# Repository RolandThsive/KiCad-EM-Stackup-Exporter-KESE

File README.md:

<div align="center">

<picture>
  <source media="(prefers-color-scheme: dark)" srcset="docs/logo/Kese_Rectangular_DarkMode.svg">
  
</picture>

**Real 3D models of KiCad boards, with the true stack-up and the copper split per net.**
Give it a `.kicad_pcb` file, get every dielectric, every net's copper and every via at its true height, ready for an EM solver or a web viewer.

KiCad's 3D export is made for mechanical fit. An EM solver needs every core and prepreg as its own body with its εr
and tanδ, copper at its real thickness, and one closed solid per net for ports. KESE reads the `.kicad_pcb` directly
(no KiCad install needed) and writes exactly that for openEMS, or for Elmer and CalculiX through FreeCAD, with each copper solid named
after its net (`Copper_GND`) and the material values in `materials.json`. The same board also comes out as a light
surface model for web viewers and renders.

<sub>The RF sensor module of <code>Generator/Input/</code>, exported in visual mode.</sub>

</div>

> [!WARNING]
> **Fill your zones before exporting.** KESE uses the zone fills KiCad stores in the board file. A ground plane or
> copper pour that has not been filled (press **B** in KiCad) and saved is left out; `report.txt` counts it under
> "zones with no fill".

## Documentation

| I want to | Read |
|---|---|
| Start | [Getting Started](https://github.com/RolandThsive/KiCad-EM-Stackup-Exporter-KESE/wiki/Getting-Started), [Project Capabilities](https://github.com/RolandThsive/KiCad-EM-Stackup-Exporter-KESE/wiki/Project-Capabilities), [Examples](https://github.com/RolandThsive/KiCad-EM-Stackup-Exporter-KESE/wiki/Examples), [Time Distribution](https://github.com/RolandThsive/KiCad-EM-Stackup-Exporter-KESE/wiki/Time-Distribution) |
| Understand it | [Working Principle](https://github.com/RolandThsive/KiCad-EM-Stackup-Exporter-KESE/wiki/Working-Principle), [Stack-Up Model](https://github.com/RolandThsive/KiCad-EM-Stackup-Exporter-KESE/wiki/Stack-Up-Model), [Output Modes](https://github.com/RolandThsive/KiCad-EM-Stackup-Exporter-KESE/wiki/Output-Modes) |
| Export for my tool | [Choosing An Export](https://github.com/RolandThsive/KiCad-EM-Stackup-Exporter-KESE/wiki/Choosing-An-Export), [KiCad And Solver Compatibility](https://github.com/RolandThsive/KiCad-EM-Stackup-Exporter-KESE/wiki/Compatibility), [openEMS Workflow](https://github.com/RolandThsive/KiCad-EM-Stackup-Exporter-KESE/wiki/OpenEMS-Workflow) |
| Know what gets modelled | [Board](https://github.com/RolandThsive/KiCad-EM-Stackup-Exporter-KESE/wiki/Board), [Copper And Traces](https://github.com/RolandThsive/KiCad-EM-Stackup-Exporter-KESE/wiki/Copper-And-Traces), [Solder Masks](https://github.com/RolandThsive/KiCad-EM-Stackup-Exporter-KESE/wiki/Solder-Masks), [Silkscreens](https://github.com/RolandThsive/KiCad-EM-Stackup-Exporter-KESE/wiki/Silkscreens), [Finish](https://github.com/RolandThsive/KiCad-EM-Stackup-Exporter-KESE/wiki/Finish), [Colorizing](https://github.com/RolandThsive/KiCad-EM-Stackup-Exporter-KESE/wiki/Colorizing) |
| Look something up | [Parameter Reference](https://github.com/RolandThsive/KiCad-EM-Stackup-Exporter-KESE/wiki/Parameter-Reference), [Checks, Errors And Warnings](https://github.com/RolandThsive/KiCad-EM-Stackup-Exporter-KESE/wiki/Checks-Errors-And-Warnings), [Material Properties](https://github.com/RolandThsive/KiCad-EM-Stackup-Exporter-KESE/wiki/Material-Properties), [Project Output Organization](https://github.com/RolandThsive/KiCad-EM-Stackup-Exporter-KESE/wiki/Project-Output-Organization), [Feature Test Collection](https://github.com/RolandThsive/KiCad-EM-Stackup-Exporter-KESE/wiki/Feature-Test-Collection), [Glossary](https://github.com/RolandThsive/KiCad-EM-Stackup-Exporter-KESE/wiki/Glossary) |
| See what is next | [Future Upgrades And Planning](https://github.com/RolandThsive/KiCad-EM-Stackup-Exporter-KESE/wiki/Future-Upgrades-And-Planning) |

## Quick Start

```bash
cd Generator
python -m pip install -r requirements.txt

python run_KESE.py                                          # Every board in Input/: the defaults, set for RF work (below)
python run_KESE.py Input/rf_module.kicad_pcb                # One board: STEP in mm at KiCad's origin, with materials.json
python run_KESE.py board.kicad_pcb --for openems            # One STL per part in mm, with materials.json
python run_KESE.py board.kicad_pcb --for viewer             # The visible surface only, GLB for web viewers
python run_KESE.py board.kicad_pcb --set Finish.FINISH_TYPE=ENIG   # A finish for a board whose file names none
python run_KESE.py board.kicad_pcb --set Copper.VIA_WALL_MM=0.02
```

The defaults are the ones for an RF analysis, so a run with no option gives a model ready for a solver: simulation
mode, a STEP file in mm at KiCad's origin, one solid per net, every ply of the laminate a solid of its own, the solder
mask and the silkscreen left out, the finish the board file names, the Djordjevic-Sarkar model for the laminate and
the Huray model for the copper in `materials.json`, and the Verifier's checks at the end. A board whose file names no
finish stops with a message that says how to name one or leave it out.

Run every command from `Generator/`, which holds the program, its settings, `Input/` and `Output/`. Edit only the
files in `Generator/parameters/` (`PCB_elements/Stackup.py` says which parts of the board are built, and each element
has a file of its own beside it), or override one value for a single run with `--set`. Each run writes a new folder,
`Output/<board>/<mode>_<FORMATS>/`, with the model files, `materials.json` (role, layer, net, z range, εr, tanδ and
conductivity of every part), `parameters.txt` and `report.txt`, and never overwrites an earlier one. The pinned
packages need Python 3.12 or later. `python -m pip install .` gives a `kese` command that works
from any folder. Full walk-through: [Getting Started](https://github.com/RolandThsive/KiCad-EM-Stackup-Exporter-KESE/wiki/Getting-Started).

## What Works

- **Input:** `.kicad_pcb` files from KiCad 4 to 10, 1 to 8 copper layers, stack-up read from Board Setup (thickness,
  εr and tanδ of every core and of every prepreg ply, copper and mask thickness, the mask's material, colours,
  finish). Footprints are read from the board file, so no libraries are needed.
- **Copper:** tracks, arcs, pads of every shape, zone fills, copper graphics (solid or hatched) and text; one solid per
  net (default), per layer, or all merged; through, blind, buried and micro vias with plated barrels; KiCad 10's
  backdrills and covered, plugged, capped and filled vias; castellated holes and edge plating; optional etch trapezoid.
- **Board:** every dielectric a solid with its own εr and tanδ, resin filling the space beside inner copper, any
  outline from `Edge.Cuts` with cut-outs and boards inside them, plated and non-plated round and slotted holes,
  KiCad 10's counterbores and countersinks.
- **Plies:** the laminate is built as it is pressed (`Stackup.FUSION_BUILD = "PLIES_SEPARATE"`, the default): one
  solid for every prepreg ply, one for every core and one for the resin between the traces of each inner copper
  layer, each with its own thickness, εr and tanδ. `"PLIES_FUSED"` keeps one solid per gap between two copper
  layers and lists its plies in `materials.json`.
- **What is built:** `parameters/PCB_elements/Stackup.py` lists the board from the top silkscreen down to the bottom
  silkscreen, and each line is `True` (built) or `False` (left out), the top and the bottom side apart.
- **For the solver:** `materials.json` also gives the frequency each εr and tanδ holds at, a Djordjevic-Sarkar (the
  default) or tabulated model of how they change with frequency, the copper's roughness (Huray values by default, or
  Hammerstad), and for
  every copper part the foil, plating, etch factor and treated face of each layer it lies on.
- **Mask, silk and finish:** solder mask conformal over every trace, pulled back from the edge and open over every
  bore that no via protection shuts; silkscreen in KiCad's own stroke font and text layout, clipped off the pads;
  ENIG, ENEPIG, HASL, lead-free HASL, OSP, immersion silver and tin, and hard gold, each metal its own layer (on by
  default, and the type the board file names; the `top_finish`, `bottom_finish` and `hole_finish` lines of
  `Stackup.py`).
- **Two modes:** `simulation` writes closed solids that touch exactly and never overlap, as GLB, STEP, STL and OBJ;
  `visual` writes only the surface you can see, as GLB and OBJ, so nothing z-fights in a viewer.
- **STEP without a CAD kernel, meshes without a mesh library:** KESE builds its own meshes and writes STEP AP214,
  GLB, STL and OBJ itself, every part under its own name; it needs only `numpy`, `shapely` and `mapbox_earcut`.
  Holes, vias, round pads and arcs go into STEP as true circles and cylinders (`Step.STEP_EXACT_ARCS`, on by
  default), in files 2.5 to 3 times smaller than flat facets.
- **Presets:** `--for freecad`, `elmer`, `calculix`, `openems`, `viewer`, `blender_glb` or `blender_obj` set mode, formats, units, origin and grouping in one go (`parameters/Run_KESE/Presets.py`).
- **Checks:** the Verifier at the end of every run (closed solids, the same volume found four ways, no overlaps, one
  visible surface; `--no-verify` leaves it out) and a regression suite that runs 47 boards through every output before a pull request.
- **Not modelled yet:** component 3D models, text boxes, dimensions, images, rigid-flex.

Every feature and every parameter is in the wiki:
[Project Capabilities](https://github.com/RolandThsive/KiCad-EM-Stackup-Exporter-KESE/wiki/Project-Capabilities),
[Copper And Traces](https://github.com/RolandThsive/KiCad-EM-Stackup-Exporter-KESE/wiki/Copper-And-Traces),
[Parameter Reference](https://github.com/RolandThsive/KiCad-EM-Stackup-Exporter-KESE/wiki/Parameter-Reference) and
[Checks, Errors And Warnings](https://github.com/RolandThsive/KiCad-EM-Stackup-Exporter-KESE/wiki/Checks-Errors-And-Warnings).

<p align="center"><sub>24 of the feature test boards of <code>featureTest/</code>, each labelled with the KiCad features it
tests and exported in visual mode. Boards whose stack-up sets no colours are given a green mask and white silkscreen
for this picture. Left out are the boards of items KESE skips (19 and 19b), the same board in five KiCad formats (20a to 20e), the boards added after the picture was made (18c and 24 to 29d), and the example boards of the
<a href="https://github.com/RolandThsive/KiCad-EM-Stackup-Exporter-KESE/wiki/Examples">Examples</a> page.</sub></p>

## Status And Next Steps

- **Validation.** The models will be compared with measured boards and with reference solver results, and corrected
  wherever they disagree.
- **Solver imports.** The routes into openEMS, and into Elmer and CalculiX through FreeCAD, follow each tool's
  documented import formats and still have to be confirmed on each tool.
- **Planned:** a web application, a desktop application, maybe a KiCad add-on, and tighter integration with openEMS or
  other solvers.

## Contributing

Help with code, bug reports, test boards, solver checks, measurements and documentation is welcome. Read
[CONTRIBUTING.md](CONTRIBUTING.md) for the code layout, the rules every change keeps and the tests to run before a pull
request.

## Licensing

Hi Sassy boy Seth, There is no greedy man here.

KESE is **free software** under the [GNU General Public License, version 3 or later](LICENSE)
(`GPL-3.0-or-later`). You may run it for any purpose, commercial work included, and study, change and share it, as long
as what you share stays under the GPL with its source. The 3D models KESE writes from your own board are generally not
covered by the GPL, in the same way a document printed by a GPL program is not.

KESE includes material derived from KiCad, which is GPL-licensed: KiCad's "newstroke" stroke font and its text layout.
KiCad's original copyright headers are kept word for word in [`licenses/`](licenses) and listed in
[NOTICE.md](NOTICE.md). Contributions are accepted under the same license; see [CONTRIBUTING.md](CONTRIBUTING.md).

KESE was checked on thousands of KiCad boards from open hardware projects; no board is part of KESE. [credits.txt](https://github.com/RolandThsive/KiCad-EM-Stackup-Exporter-KESE/blob/corpus-testing/credits.txt)
thanks their authors and names each project's license, as does the wiki's
[Credits](https://github.com/RolandThsive/KiCad-EM-Stackup-Exporter-KESE/wiki/Credits) page.

**Contact (only through these channels):**
[Email](mailto:rolandthsive@yahoo.com) ·
[GitHub](https://github.com/RolandThsive) ·
[MyAnimeList](https://myanimelist.net/profile/RolandThsive) ·
[Instagram](https://www.instagram.com/ro_h_bots)

---

<div align="center">

## About Me

A traveller and mechatronics engineer who loves building machines that move, from the mechanics to the electronics
and the firmware. Trained in mechanical design and robotics, with a research master's in mechatronics, I have built
robotic hands, a humanoid torso, industrial bin-picking cells and rocket electronics, designing PCBs in KiCad and
firmware for STM32 and Espressif chips.

I put my full time into building industrial-grade software and making well-researched but hard-to-find scientific
knowledge free for everyone. KESE exists so that a board designed in KiCad can go straight into an EM solver without
being rebuilt by hand in CAD. I will keep maintaining it until it becomes the go-to bridge from KiCad to EM
simulation, with models that match real, fabricated boards.

**[Website](https://ro-h-bots.blogspot.com/)** ·
**[Instagram](https://www.instagram.com/ro_h_bots)** ·
**[MyAnimeList](https://myanimelist.net/profile/RolandThsive)** ·
**[Email](mailto:rolandthsive@yahoo.com)**

*Contributions of every kind are welcome. Together we can make this the reference tool for turning KiCad boards into
EM-ready models.*

</div>

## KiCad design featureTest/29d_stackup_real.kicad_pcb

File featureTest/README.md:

# Feature Test Boards

One small board per group of KiCad features that KESE reads. Each board is made by
`Generator/tests/feature_boards/make.py`; change a board there and run it again rather than
editing these files by hand:

```bash
cd Generator
python tests/feature_boards/make.py
```

The regression suite (`Generator/tests/test_boards.py`) runs every board here through every
output; after changing a board, run `python tests/test_boards.py --accept` to record it again.

Boards in KiCad 7's format were read back, zone-filled and saved by KiCad 7 itself, so they are
exactly what KiCad writes, including the outlines of TrueType text. That needs KiCad 7's Python
module (`pcbnew`): without it, `make.py` writes the boards as built, with unfilled zones, over the
saved ones (on a machine without KiCad, 31 files change). Run it where KiCad 7 is installed, or
put the saved boards back with `git checkout featureTest`. Features that only KiCad 8, 9 or 10
have are on hand-written boards in that version's format, written from KiCad's own file writer
source; open those once in that KiCad to confirm they load. One board (`29c`) is in the format
after KiCad 10, which a development build (10.99) writes: KESE reads it with a warning that the
format is newer than the ones it is tested with.

| File | Format | What it covers |
|---|---|---|
| `01_holes_slotted.kicad_pcb` | KiCad 7 (saved by KiCad 7) | Plated and non-plated slots: horizontal, vertical, rotated pad, rotated and flipped footprint, rectangular pad, long slot, a slot as wide as it is long, an offset slot. |
| `02_holes_round.kicad_pcb` | KiCad 7 (saved by KiCad 7) | Round plated holes of several sizes and pad shapes, an offset drill, non-plated holes with and without a copper ring, and a plated hole in a footprint on the back. |
| `03_vias_through.kicad_pcb` | KiCad 7 (saved by KiCad 7) | Through vias from 0.3 to 2 mm, a chain of vias on one net, vias in pads, a via on the board edge, a free via; vias left open in the mask (viasonmask true). |
| `03b_vias_k10.kicad_pcb` | KiCad 10 (hand-written) | KiCad 10's via options on four layers: tented on both sides, on the front only, open, and left to the board's setting on one side; covered, plugged, capped and filled vias; a backdrill from the bottom and one from the top, a counterbore and a countersink; blind, buried and micro vias; vias that keep only their start and end rings or drop unused rings; and a plated pad with a backdrill and mounting holes with a counterbore and a countersink. |
| `04_vias_blind_buried.kicad_pcb` | KiCad 7 (saved by KiCad 7) | Six layers: a through via, blind vias from each side, a buried via, and through vias and a plated pad that drop their unused rings. |
| `05_vias_micro.kicad_pcb` | KiCad 7 (saved by KiCad 7) | Eight layers: microvias on each side, a stack of microvias over a buried via, and the same levels staggered. |
| `06_padstacks.kicad_pcb` | KiCad 10 (hand-written) | KiCad 10's padstacks on four layers: a plated pad and a via with one shape on the front, another on the inner layers and a third on the back; a pad and a via with their own shape on every copper layer; a normal pad and via beside them, and inner tracks to the inner rings. |
| `07_pad_shapes.kicad_pcb` | KiCad 7 (saved by KiCad 7) | Every pad shape: circle, rect, oval, rounded rect, trapezoid, chamfered, chamfered and rounded, custom pads on a circle and a rect anchor; rotated pads, a footprint at 45 degrees and one on the back; mask-only and paste-only aperture pads, an edge-connector pad and a pad with no net. |
| `08_copper_graphics.kicad_pcb` | KiCad 7 (saved by KiCad 7) | Lines, rectangles, circles (open and filled), an arc, polygons (filled, open, and one with an arc edge) and a Bezier curve drawn on F.Cu and B.Cu with no net, as KiCad 7 has them; the same shapes in a footprint at 30 degrees and in one on the back; a track that ends on a drawing. |
| `08b_copper_graphics_nets.kicad_pcb` | KiCad 10 (hand-written) | KiCad 10's copper drawings: shapes that belong to a net, copper left bare by the solder mask (a rectangle, a track and an arc track, with and without a mask margin), rectangles with rounded corners, hatched, reverse-hatched and cross-hatched fills, and a board outline drawn as one rectangle with rounded corners. |
| `09_copper_text.kicad_pcb` | KiCad 7 (saved by KiCad 7) | Text on copper: the stroke font plain, bold, italic, rotated, on two lines and justified; TrueType text (DejaVu Sans) on F.Cu and mirrored on B.Cu, bold and italic; knockout text; a text box; footprint text with a hidden value and a ${REFERENCE} variable. |
| `10_tracks_arcs.kicad_pcb` | KiCad 7 (saved by KiCad 7) | Tracks 0.1 to 2 mm wide, arc tracks of 90 and 180 degrees and an almost straight one, a segment-arc-segment chain, a zero-length track, two nets that cross (a short), overlapping tracks of one net, a 1 um track, a T and an acute junction, tracks and an arc on B.Cu. The crossing tracks end on pads of their own nets: without them KiCad gives both the same net. |
| `11_zones.kicad_pcb` | KiCad 7 (saved by KiCad 7) | Four layers of zones: thermal reliefs and a solid connection to the same pads, pads that override the zone's connection, a pad of another net inside a zone, hatched fills at 0 and 45 degrees, a zone split in two by a track with its island kept on In1 and removed on In2, a zone on two layers with a cut-out, zones of two priorities overlapping, a zone left unfilled, and a keepout area that a zone flows around. |
| `12_outline_shapes.kicad_pcb` | KiCad 7 (saved by KiCad 7) | An outline of lines, rounded corners (arcs), a Bezier edge and a notch; cut-outs drawn as a circle, a rectangle, a polygon, a slot of two lines and two arcs, a rectangle of four lines whose ends miss by 3 nm, and a circle and a rectangle on Edge.Cuts inside a footprint at 30 degrees; zones on both sides that KiCad fills up to the outline and around the cut-outs. |
| `13a_outline_none.kicad_pcb` | KiCad 7 (saved by KiCad 7) | No Edge.Cuts at all: two plated pads joined by a track, and a via. |
| `13b_outline_two.kicad_pcb` | KiCad 7 (saved by KiCad 7) | Two separate boards in one file, one of them with a square hole that has a third, small board inside it. |
| `14_stackup_full.kicad_pcb` | KiCad 7 (saved by KiCad 7) | A four-layer stack-up with everything KiCad 7 lets you set: coloured mask and silk, a mask material with its permittivity, copper of 35, 17.5, 17.5 and 70 um, a prepreg of two sublayers, a core and a prepreg of different materials, an ENIG finish and impedance-controlled dielectrics. |
| `15_stackup_none.kicad_pcb` | KiCad 7 (saved by KiCad 7) | Four copper layers, no stack-up in the file (as older KiCad boards have), and a board thickness of 1.2 mm in the general section. |
| `16_edge_plating_castellation.kicad_pcb` | KiCad 7 (saved by KiCad 7) | Castellated pads (pad property castellated) on the right edge, with their holes on the edge, a plated board edge (edge_plating yes, castellated_pads yes) with GND tracks running along the left edge, a GND zone, and an immersion silver finish. |
| `16b_edge_plating_border.kicad_pcb` | KiCad 7 (saved by KiCad 7) | A plated board edge (edge_plating yes) as RF boards have it: a GND border 1.2 mm wide on every copper layer along the rounded outline and 1.0 mm wide around a rounded cut-out, the solder mask open over it on both sides, a fence of GND vias in the border, GND planes on F.Cu, In1.Cu and B.Cu, a +3V3 plane on In2.Cu, plated mounting holes, and a few parts. Green mask, white silk, ENIG. |
| `17_mask_silk.kicad_pcb` | KiCad 7 (saved by KiCad 7) | Solder mask openings from the board's pad-to-mask clearance, a footprint's margin, a pad's own margin and a negative one; plated pads; openings drawn on F.Mask and B.Mask (a rectangle over a track, a circle, a polygon, text); a tented via; silkscreen lines, shapes and text on both sides, TrueType silk text, and a silk outline drawn across pads. Red mask, black silk, lead-free HASL. |
| `17b_silk_over_copper.kicad_pcb` | KiCad 7 (saved by KiCad 7) | Silkscreen over copper: text and a line printed across four tracks 0.25 to 2 mm wide on F.Cu, and a line across the same tracks on B.Cu, so the ink rides over the mask on the copper; a footprint whose silk outline runs across its pads, a silk circle across a through-hole pad, and silk text across an opening drawn on F.Mask (for SILKSCREEN_OVER_COPPER). White mask, black silk, ENIG. |
| `18_finishes.kicad_pcb` | KiCad 7 (saved by KiCad 7) | Gold edge fingers: edge-connector pads on both sides running to a bevelled card edge (edge_connector bevelled), with a hard gold finish. |
| `18b_finish_pads.kicad_pcb` | KiCad 7 (saved by KiCad 7) | Surface finish on every kind of bare copper: an eight-pin SOIC-style footprint, a 3 mm square pad, a two-pin through-hole header (finish on both faces), a track left bare by an opening drawn on F.Mask, a tented via, and a round pad on the bottom. Pad-to-mask clearance 0.05 mm. Green mask, white silk, ENIG. |
| `18c_finish_before_mask.kicad_pcb` | KiCad 7 (saved by KiCad 7) | Surface finish applied before the solder mask (run with Finish.FINISH_BEFORE_SOLDER_MASK = True): SMD pads with the board's clearance and one with a negative mask margin, a track under the mask with silkscreen printed across it, a tented via to a round pad on the bottom, a through-hole header, and a GND zone on B.Cu with a thermal pad in it, so the finish lies on all the copper and the mask and ink lie on the finish. Blue mask, white silk, ENEPIG. |
| `19_skipped_items.kicad_pcb` | KiCad 7 (saved by KiCad 7) | Dimensions (aligned on F.Cu, orthogonal, leader, center and radial on silk), targets on F.Cu and silk, a group of a copper rectangle, a track and silk text, a footprint with a 3D model, a picture on silk, and text boxes on F.Cu and on silk. |
| `19b_skipped_items_k10.kicad_pcb` | KiCad 10 (hand-written) | KiCad 10's table (on F.Cu), QR codes on silk and on F.Cu, points on F.Cu and on a user layer, and a reference image. |
| `20a_format_kicad6.kicad_pcb` | KiCad 6 (hand-written) | The same small board in KiCad 6, 7, 8, 9 and 10's format: a plated pad and a rounded SMD pad in a footprint, a pad on the back of a turned footprint, a track, a via and an arc track, a GND zone on the back, and silkscreen and copper text. |
| `20b_format_kicad7.kicad_pcb` | KiCad 7 (saved by KiCad 7) | The same small board in KiCad 6, 7, 8, 9 and 10's format: a plated pad and a rounded SMD pad in a footprint, a pad on the back of a turned footprint, a track, a via and an arc track, a GND zone on the back, and silkscreen and copper text. |
| `20c_format_kicad8.kicad_pcb` | KiCad 8 (hand-written) | The same small board in KiCad 6, 7, 8, 9 and 10's format: a plated pad and a rounded SMD pad in a footprint, a pad on the back of a turned footprint, a track, a via and an arc track, a GND zone on the back, and silkscreen and copper text. |
| `20d_format_kicad9.kicad_pcb` | KiCad 9 (hand-written) | The same small board in KiCad 6, 7, 8, 9 and 10's format: a plated pad and a rounded SMD pad in a footprint, a pad on the back of a turned footprint, a track, a via and an arc track, a GND zone on the back, and silkscreen and copper text. |
| `20e_format_kicad10.kicad_pcb` | KiCad 10 (hand-written) | The same small board in KiCad 6, 7, 8, 9 and 10's format: a plated pad and a rounded SMD pad in a footprint, a pad on the back of a turned footprint, a track, a via and an arc track, a GND zone on the back, and silkscreen and copper text. |
| `24_backdrills.kicad_pcb` | KiCad 10 (hand-written) | KiCad 10's backdrills on six layers: from the back down to each inner layer and from the front (tertiary drills), both on one via, through the whole board, as wide as the pad, narrower than the hole, starting and ending on the same layer, on a blind via and through a track that leaves the drilled-out layer; plated pads with a backdrill and a tertiary drill, a non-plated hole stepped by one, and drills KESE leaves out as KiCad does: on an SMD pad, with no size, and to a layer the board does not have. |
| `25_post_machining.kicad_pcb` | KiCad 10 (hand-written) | KiCad 10's counterbores and countersinks on four layers. Mounting holes counterbored from the front and from the back, deeper than the board and to a floor inside an inner copper layer; countersunk at 82, 90, 100 and 120 degrees, from the back, to a depth short of the cone's tip, and smaller than the hole (nothing to cut). A plated pad counterbored on the front and countersunk on the back, a pad whose counterbore is centred on the pad off its offset drill, vias counterbored and countersunk, and what KESE leaves out as KiCad does: a counterbore with no depth, a countersink with no angle, and one on an SMD pad. |
| `26_via_protection.kicad_pcb` | KiCad 10 (hand-written) | KiCad 10's via protection (IPC-4761) on four layers: Types I to VII on the front, then on both faces (tented, tented and covered, plugged, plugged and covered, filled, filled and covered, filled and capped); a via left to the board's setting (plugged on the back), covered but not tented, capped with no fill, filled and backdrilled, plugged and counterbored on the same face, a filled blind via, a filled and capped buried via (a cap needs an outer end) and a blind via covered at its inner end (no effect). |
| `27_hatched_fills.kicad_pcb` | KiCad 10 (hand-written) | KiCad 10's hatched fills on two layers. Hatched, reverse-hatched and cross-hatched rectangles, a rectangle with rounded corners, circles and polygons on copper (with a net), silkscreen and the solder mask, at pen widths from 0.1 to 0.5 mm; copper left bare by the mask under a hatch; the hatch cut back around board text, a line, an overlapping hatched shape, a text box and another footprint's reference, but not around a footprint's own reference or another footprint's other text; a turned footprint with hatched drawings; a hatch too fine for its size, held to about 100 lines; a hatch drawn with no pen (nothing), a hatched custom pad shape (solid) and a hatched board outline (the outline only). |
| `28_plated_edge_machining.kicad_pcb` | KiCad 10 (hand-written) | KiCad 10's post machining, backdrills and blind vias at a plated board edge (edge_plating yes) on four layers: a counterbore from the front and a countersink from the back that cross the edge while their holes stay inside, a via backdrilled from the back and a plated pad drilled from the front (a tertiary drill) wider than their rings, both crossing the edge, and blind vias from the front that reach into the plating; GND tracks along the left edge give the plating its net. Each cuts the plating only between its own heights. |
| `29_stackup_plies.kicad_pcb` | KiCad 7 (saved by KiCad 7) | Six layers whose gaps are laid up of plies, as KiCad's stack-up editor writes them (the sub-layers of a dielectric): a 1080 ply on a 2116 ply under F.Cu and the same mirrored over B.Cu, a core of one ply, three equal 7628 plies between In2.Cu and In3.Cu, and a core with a bond film of half a micrometre, thinner than KESE builds on its own. A through via, a blind via from each side, a buried via through the three equal plies and one through both cores, a plated and a non-plated hole, a track on every layer and GND planes on In2.Cu and In3.Cu. |
| `29b_stackup_plies_machined.kicad_pcb` | KiCad 10 (hand-written) | KiCad 10's machining in a laminate of plies (four layers, a 2116 and a 1080 ply on each side of one core). Counterbores from the front, their depth from the top of F.Cu: to a floor inside the first ply (0.1 mm), exactly between the two plies (0.159 mm), inside the second ply (0.2 mm), inside In1.Cu and the resin beside it (0.243 mm) and inside the core (0.5 mm); the same from the back into the outer ply and to the join of the plies; a countersink from each side; vias with a backdrill and a tertiary drill through both plies, a counterbored via, blind vias through the plies and a buried via through the core, and a counterbored plated pad. |
| `29c_stackup_frequency.kicad_pcb` | KiCad 10.99 (hand-written) | What the format after KiCad 10 adds to every ply of a dielectric (file format 20260511): the frequency its er and loss tangent hold at (spec_frequency, in Hz) and how they change with frequency (dielectric_model constant or djordjevic_sarkar). Four layers: a 2116 ply with the Djordjevic-Sarkar model at 1 GHz on a 1080 ply with constant values, a core with the model at 10 GHz, a 1080 ply with the model at 5 GHz on a 2116 ply with constant values at 2.5 GHz, and a solder mask of another material on each side. |
| `29d_stackup_real.kicad_pcb` | KiCad 7 (saved by KiCad 7) | A fabricator's four-layer build as it is pressed (JLCPCB's JLC04161H-2116C, 1.6 mm): under each outer copper a 2116 ply of 0.124 mm (er 4.16) and a 1080 ply of 0.0764 mm (er 3.91), a core of 1.065 mm, inner copper of 15.2 um and outer copper of 35 um. A microstrip between two launch pads over a GND plane on In1.Cu, GND copper beside it with a fence of vias, a +3V3 plane on In2.Cu fed through a via, a decoupling capacitor, a header, and tracks on the back. Green mask, white silk, ENIG. |

## Example Boards

The three example boards of `Generator/Input/` are here too, so that the regression suite runs
them with the boards above. Each is a whole board that uses many of these features at once.
`make.py` does not make them, and does not write this section when it rewrites this README.

| File | Format | What it shows |
|---|---|---|
| `21_rf_module.kicad_pcb` | KiCad 7 (saved by KiCad 7) | A 4-layer RF sensor module with a plated edge (edge_plating yes): a GND border on every copper layer along the rounded outline and around a cut-out, the mask open over it, and a fence of GND vias in it. A QFN-32 microcontroller with its crystal, a 6-pad SWD connector and a SOIC-8 flash; a QFN-20 radio on an SPI bus, its 50 ohm line through a matching network to a coax connector between rows of stitching vias; an LDO fed from a 6-pin header, three LEDs, test points on both sides, GND planes on F.Cu, In1.Cu and B.Cu, In2.Cu split into +3V3 and +5V, plated mounting holes, silkscreen on both sides, and the KESE logo of docs/logo on the back in bare copper, copper under the mask and silkscreen. Blue mask, white silk, ENIG. |
| `22_hdi_module.kicad_pcb` | KiCad 7 (saved by KiCad 7) | A 6-layer HDI radio module, 1+4+1: microvias from each outer layer to the layer under it, buried vias from In1.Cu to In4.Cu, blind vias from an outer layer to In2.Cu or In3.Cu, and through vias, on a stack-up of named glass styles with an LPI mask and dielectric constraints. A 64-ball BGA with a microvia in the pad of each inner ball and its supplies on staggered buried vias, fanned out on In1.Cu to 43 castellated pads (castellated_pads yes) on three sides; a USON-8 flash, a 2016 crystal, a buck converter making +1V1, and a matching network feeding a meander antenna in a keep-out, its line referenced to In2.Cu through a cut in In1.Cu. GND on In2.Cu, +3V3 on In3.Cu and a +1V1 island on In4.Cu; on the back an exposed GND pad, test pads reached on In4.Cu, the pin numbers and the KESE logo. Black mask, white silk, immersion silver. |
| `23_pcie_card.kicad_pcb` | KiCad 7 (saved by KiCad 7) | A 4-layer PCIe x1 gigabit Ethernet card that powers its port (PoE), within a low-profile card's size: gold fingers on both sides at a 1.00 mm pitch on a bevelled tongue (edge_connector bevelled), PRSNT1# and PRSNT2# 1 mm shorter and joined by a single trace, no plane under the fingers and a bulk capacitor at them for each supply (PCI Express CEM Rev 2.0). A QFN-48 controller with its crystal, EEPROM and +1V0 LDO, the PCIe lane and clock pairs length matched by meanders, AC coupling capacitors on the card's transmit pair; an RJ45 jack with magnetics at the bracket, a 12 V fan header and an SMBus temperature sensor. Across a 2 mm band kept clear on every copper layer, and a slot, the PoE side: 48 V in through a fuse to a PSE controller switching the port through a MOSFET, its own PGND and +48V planes, and optocouplers across the slot. GND on F.Cu, In1.Cu and B.Cu, +3V3 and a +1V0 island on In2.Cu, the KESE logo on the front. Where finger B1 sits from the bracket and the outline next to the bracket are estimates. Green mask, white silk, hard gold. |

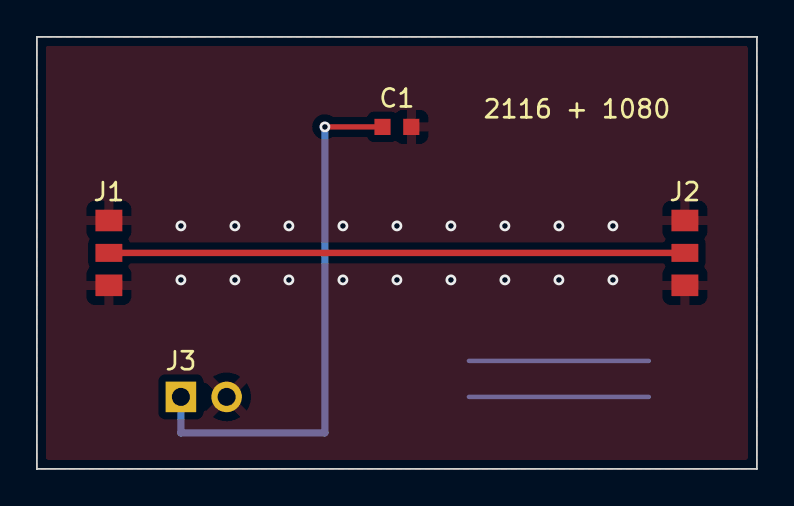
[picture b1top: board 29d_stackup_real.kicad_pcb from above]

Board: 4 copper layers, 40.0 x 24.0 mm, 4 parts (0 on the bottom side), 3 nets.

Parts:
C1: C0603
J1, J2: RFLaunch
J3: Header

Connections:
+3V3: C1.1, J3.1
GND: C1.2, J1.2, J1.3, J2.2, J2.3, J3.2
RF: J1.1, J2.1

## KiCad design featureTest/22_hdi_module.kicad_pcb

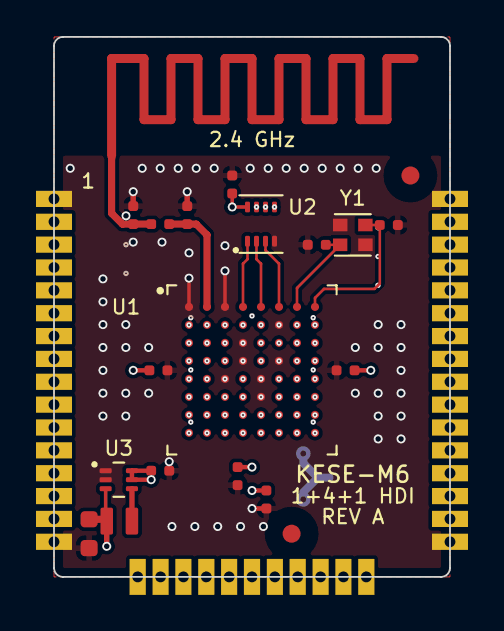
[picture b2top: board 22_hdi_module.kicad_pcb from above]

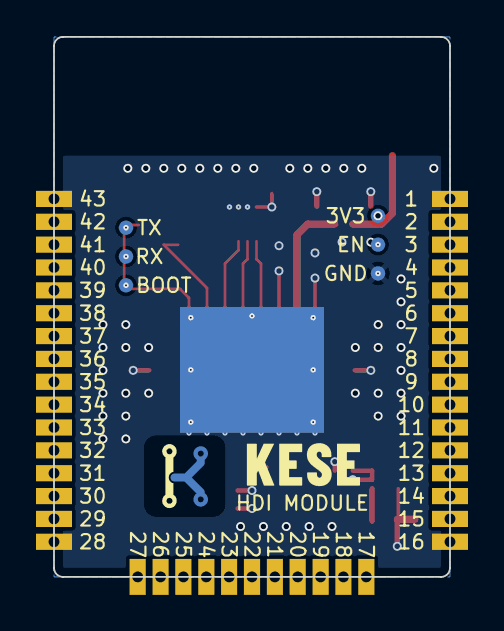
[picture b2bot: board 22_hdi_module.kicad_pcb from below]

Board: 6 copper layers, 22.0 x 30.0 mm, 30 parts (7 on the bottom side), 50 nets.

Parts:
AE1: Antenna_Meander_2.4GHz
C1, C2, C3, C4, C5, C6, C9, C10, C20, C21: 0402
C7: 0603
EP: Module_GND_Pad_8x7mm
FID1, FID2: Fiducial_1mm
J1, J3: Castellated_1x16_P1.27mm
J2: Castellated_1x11_P1.27mm
L1: L_2016
L20: 0402
TP1, TP2, TP3, TP4, TP5, TP6: TestPad_0.8mm
U1: BGA-64_9x9mm_P1.0mm
U2: USON-8_2x3mm_P0.5mm
U3: SOT-563
Y1: Crystal_2016

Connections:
+1V1: C2.1, C7.1, L1.1, U1.C5, U1.D3, U1.D5, U1.E4, U1.E6, U1.F4, U3.3
+3V3: C1.1, C5.2, C6.1, C9.1, C10.2, J1.2, J2.22, J3.42, TP2.1, U1.C3, U1.C6, U1.F3, U1.F6, U2.8, U3.5, U3.6
ANT: AE1.1, C21.2, L20.1
BOOT: J3.39, TP6.1, U1.C8
EN: J1.3, TP1.1, U1.B1
GND: C1.2, C2.2, C3.1, C4.2, C5.1, C6.2, C7.2, C9.2, C10.1, C20.1, C21.1, EP.EP, J1.1, J1.16, J3.28, J3.43, TP3.1, U1.A1, U1.A3, U1.B6, U1.C4, U1.D4, U1.D6, U1.E3, U1.E5, U1.F5, U2.4, U3.1, U3.2, Y1.2, Y1.4
IO1: J1.4, U1.B2
IO2: J1.5, U1.C1
IO3: J1.6, U1.C2
IO4: J1.7, U1.D1
IO5: J1.8, U1.D2
IO6: J1.9, U1.E1
IO7: J1.10, U1.E2
IO8: J1.11, U1.F1
IO9: J1.12, U1.F2
IO10: J1.13, U1.G1
IO11: J1.14, U1.G2
IO12: J1.15, U1.H1
IO13: J3.38, U1.C7
IO14: J3.37, U1.D8
IO15: J3.36, U1.D7
IO16: J3.35, U1.E8
IO17: J3.34, U1.E7
IO18: J3.33, U1.F8
IO19: J3.32, U1.F7
IO20: J3.31, U1.G8
IO21: J3.30, U1.G7
IO22: J3.29, U1.H8
IO23: J2.19, U1.H3
IO24: J2.20, U1.G4
IO25: J2.21, U1.H4
IO26: J2.23, U1.G5
IO27: J2.24, U1.H5
IO28: J2.25, U1.G6
IO29: J2.26, U1.H6
IO30: J2.27, U1.H7
RF: C20.2, L20.2, U1.A2
RXD0: J3.40, TP5.1, U1.B7
SPI_CLK: U1.B4, U2.6
SPI_CS: U1.A4, U2.1
SPI_DI: U1.B5, U2.5
SPI_DO: U1.A5, U2.2
SPI_HOLD: U1.B3, U2.7
SPI_WP: U1.A6, U2.3
SW: L1.2, U3.4
TXD0: J3.41, TP4.1, U1.B8
USB_DN: J2.17, U1.H2
USB_DP: J2.18, U1.G3
XIN: C3.2, U1.A7, Y1.1
XOUT: C4.1, U1.A8, Y1.3

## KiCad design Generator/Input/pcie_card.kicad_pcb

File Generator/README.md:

# KESE

This folder is KiCad EM Stackup Exporter (KESE) itself: the program, its settings, its tests and
the boards it reads and writes. The rest of the repository is its documentation and licences.
What KESE does, its examples and its licence are in the [main README](../README.md).

| Path | What It Is |
|---|---|
| `run_KESE.py` | Runs KESE from this folder without installing it |
| `kese/` | The program: nine stages that run in order, plus `core/` and `model/` |
| `parameters/` | Every setting (the only files you edit), in three folders: `PCB_elements/` for what the board is made of, with `Stackup.py` saying which parts are built, `Run_KESE/` for how KESE runs, and `Fileformats/` for the files it writes |
| `Input/` | Boards to export (three examples included) |
| `Output/` | One folder per board and run |
| `tests/` | The layout rules, the regression suite with its test boards and baseline, the other tests, and `feature_boards/`, which makes the boards in `featureTest/` |
| `tools/` | Scripts for the repository itself: `make_swatches.py` makes the wiki's colour boxes, `font_lines.py` rewrites a stroke font as JSON Lines, a glyph per line |
| `pyproject.toml`, `requirements.txt` | The package, and the Python packages it was tested with |

## Quick Start

```bash
cd Generator
python -m pip install -r requirements.txt     # Python 3.12 or later
python run_KESE.py                            # Every board in Input/, settings from parameters/
python run_KESE.py --help                     # Every option
```

Run the commands from this folder: `Input/` and `Output/` are found from the folder you run in.
`python -m pip install .` here gives a `kese` command that works from any folder.

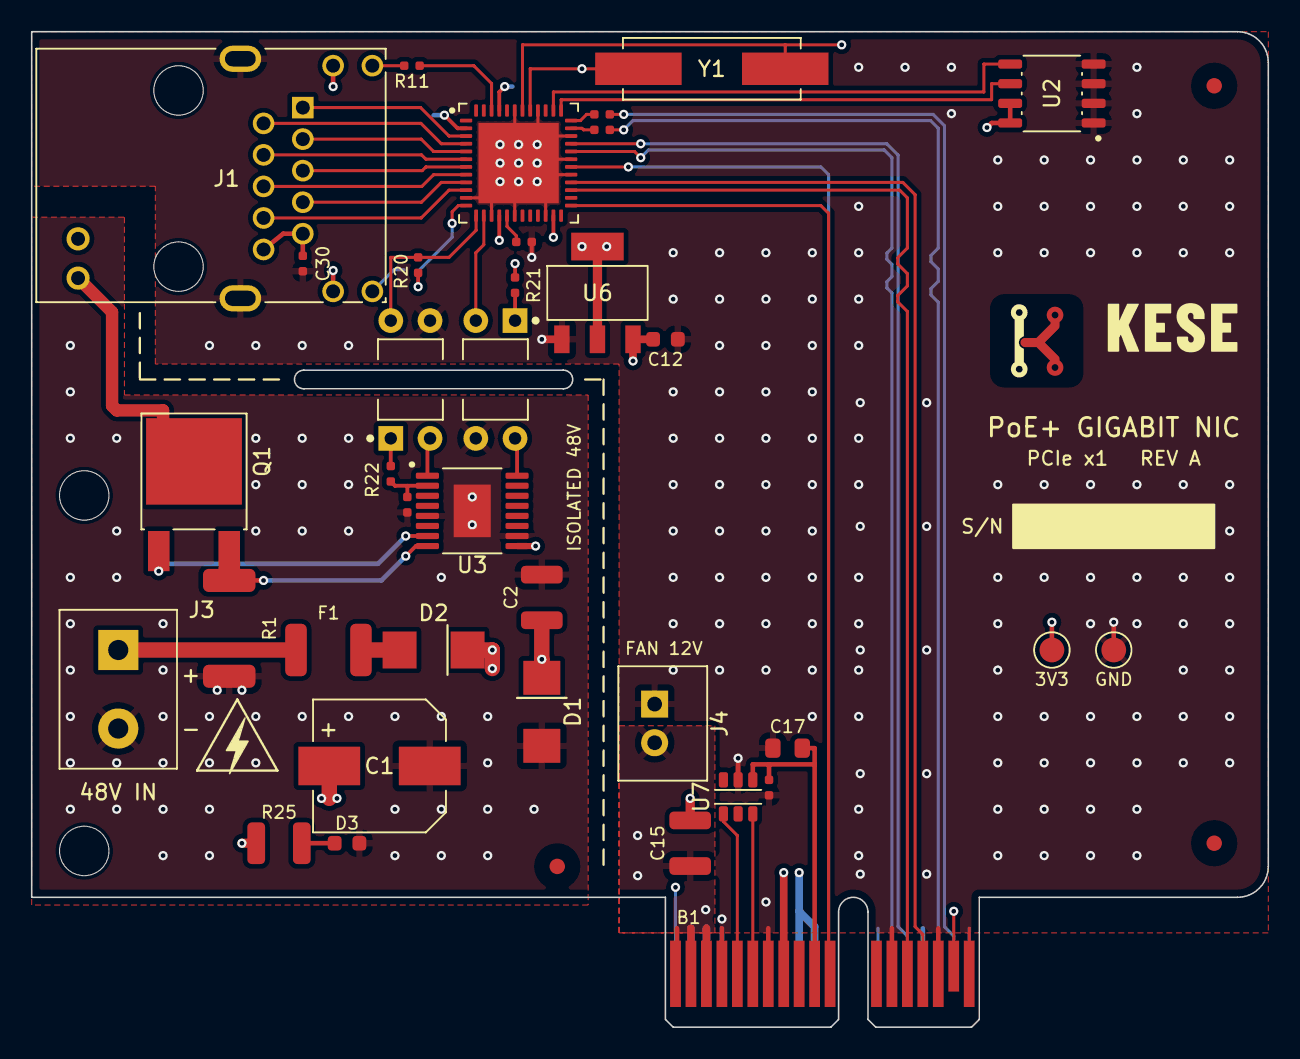
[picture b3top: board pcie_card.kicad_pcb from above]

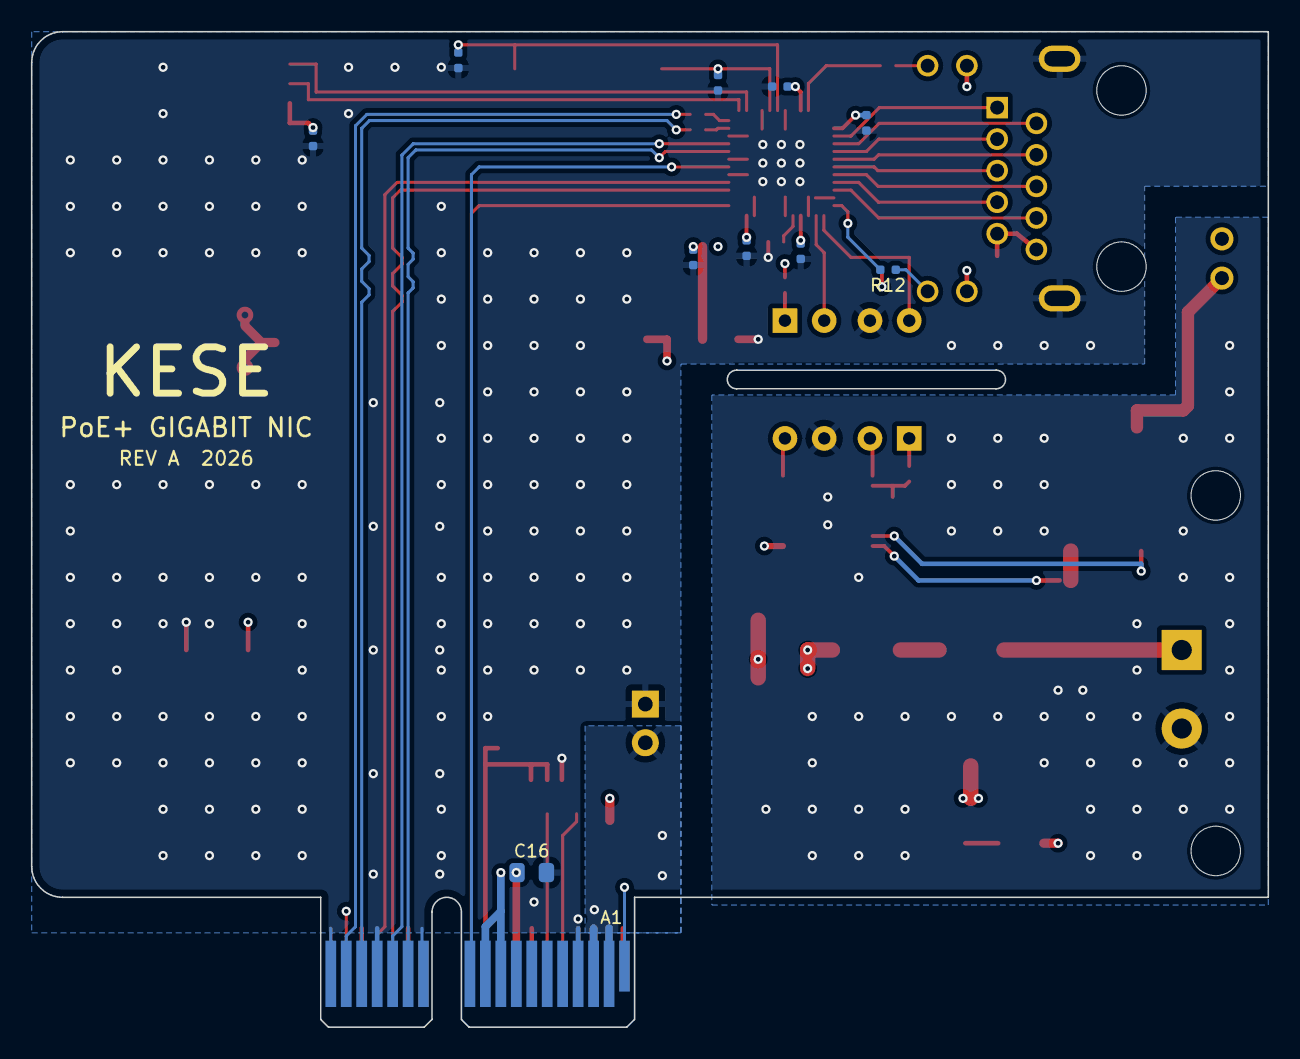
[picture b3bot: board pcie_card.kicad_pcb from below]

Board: 4 copper layers, 80.0 x 64.4 mm, 51 parts (10 on the bottom side), 51 nets.

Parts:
C1: CP_Elec_8x10
C2, C15: 1210
C3, C4, C6, C7, C8, C9, C10, C13, C14, C21, C22, C24, C30: 0402
C12: 0603
C16, C17: 0805
D1, D2: D_SMB
D3: 0603
F1: 1812
FID1, FID2, FID3: Fiducial_1mm
H1, H2: MountingHole_3.2mm
J1: RJ45_MagJack_PoE
J3: TerminalBlock_1x02_P5.08mm
J4: JST_XH_1x02_P2.5mm
J5: PCIe_x1_EdgeConnector
Q1: TO-252-2_DPAK
R1: 2512
R10, R11, R12, R20, R21, R22: 0402
R25: 1210
TP1, TP2: TestPoint_1.6mm
U1: QFN-48_7x7mm_P0.5mm
U2: SOIC-8_3.9x4.9mm
U3: TSSOP-16_4.4x5mm_EP
U4, U5: DIP-4_W7.62mm
U6: SOT-223-3_TabPin2
U7: SOT-23-6
Y1: Crystal_HC49-SMD

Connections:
+1V0: C7.1, C9.1, C13.1, U1.23, U1.45, U6.2, U6.4
+3V3: C6.1, C8.1, C10.1, C12.1, C16.2, J1.13, J1.15, J5.A9, J5.A10, J5.B8, R20.2, R21.1, TP1.1, U1.2, U1.16, U2.7, U2.8, U6.3
+3V3AUX: C14.1, C17.2, J5.B10, U7.4
+12V: C15.2, J4.2, J5.A2, J5.A3, J5.B1, J5.B2, J5.B3
+48V: C1.1, C2.2, D1.1, D2.2, J1.11, R25.1, U3.9
EE_SCL: U1.37, U2.6
EE_SDA: U1.38, U2.5
GATE: Q1.1, U3.7
GND: C3.2, C4.2, C6.2, C7.2, C8.2, C9.2, C10.2, C12.2, C13.2, C14.2, C15.1, C16.1, C17.1, C30.2, J1.SH, J4.1, J5.A4, J5.A12, J5.A15, J5.A18, J5.B4, J5.B7, J5.B13, J5.B16, J5.B18, R10.2, TP2.1, U1.11, U1.15, U1.18, U1.22, U1.29, U1.31, U1.34, U1.40, U1.43, U1.49, U2.1, U2.2, U2.3, U2.4, U4.3, U6.1, U7.5
LED1_K: J1.14, R11.1
LED2_K: J1.16, R12.1
LED48: D3.1, R25.2
LED_ACT#: R12.2, U1.12
LED_LINK#: R11.2, U1.46
MDI0N: J1.2, U1.4
MDI0P: J1.1, U1.3
MDI1N: J1.4, U1.6
MDI1P: J1.3, U1.5
MDI2N: J1.6, U1.8
MDI2P: J1.5, U1.7
MDI3N: J1.8, U1.10
MDI3P: J1.7, U1.9
MDI_CT: C30.1, J1.9, J1.10
OPTO_A: R22.1, U4.1
P3V3: C24.1, R22.2, U3.2
PERN: C22.1, U1.36
PERN0: C22.2, J5.A17
PERP: C21.1, U1.35
PERP0: C21.2, J5.A16
PERST#: J5.A11, U1.30
PETN0: J5.B15, U1.28
PETP0: J5.B14, U1.27
PGND: C1.2, C2.1, C24.2, D1.2, D3.2, J3.2, R1.2, U3.5, U3.10, U3.17, U5.3
POE_EN#: U1.14, U5.2
POE_INT#: R20.1, U1.13, U4.4
POE_RTN: J1.12, Q1.2
PRSNT#: J5.A1, J5.B17
PSE_EN: U3.16, U5.4
PSE_INT: U3.1, U4.2
REFCLK+: J5.A13, U1.32
REFCLK-: J5.A14, U1.33
RSET: R10.1, U1.17
SENSE: Q1.3, R1.1, U3.8
SMCLK: J5.B5, U7.1
SMDAT: J5.B6, U7.3
U5_A: R21.2, U5.1
VFUSE: D2.1, F1.2
VIN: F1.1, J3.1
WAKE#: J5.B11, U1.25
XI: C4.1, U1.42, Y1.2
XO: C3.1, U1.41, Y1.1
